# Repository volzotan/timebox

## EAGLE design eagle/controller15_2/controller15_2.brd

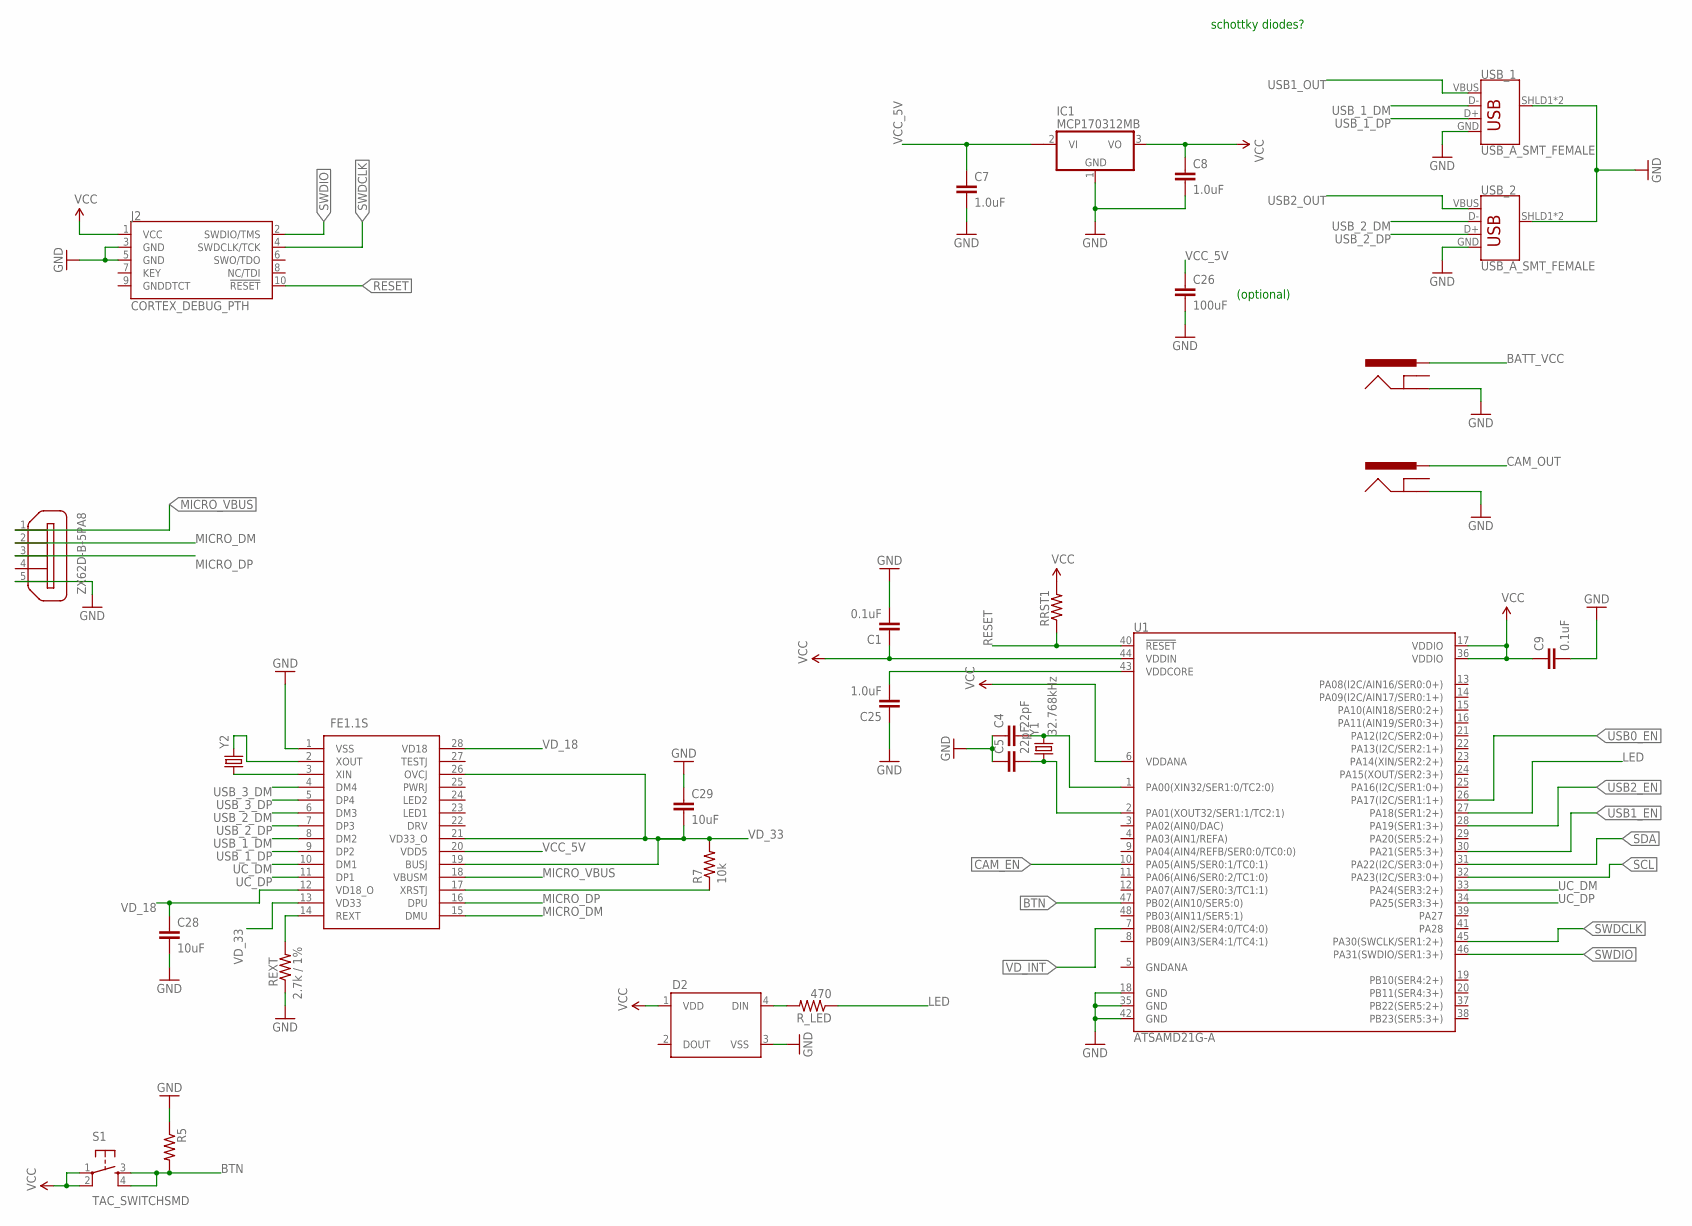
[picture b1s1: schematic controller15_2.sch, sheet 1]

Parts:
C1, C9: 0.1uF; 0805
C4, C5: 22pF; 0805
C7, C8: 1.0uF; 1206
C25: 1.0uF; 0805
C26: 100uF; 1206
C28, C29: 10uF; 0805
D2: WS2812B
IC1: MCP170312MB; SOT89
IC3: FE1.1S; SOP64P600X175-28N
J2: CORTEX_DEBUG_PTH; 2X5-PTH-1.27MM
J3, J4: POWER_JACKPTH_BREAD; POWER_JACK_PTH_BREAD
R5: RESISTOR0805-RES; 0805
R7: 10k; 0805
REXT: 2.7k / 1%; 0805
RRST1: RESISTOR0805-RES; 0805
R_LED: 470; 0805
S1: TAC_SWITCHSMD; TACTILE-SWITCH-SMD
U1: ATSAMD21G-A; TQFP-48
USB_1, USB_2: USB_A_SMT_FEMALE; USB-A-S-SILK-FEMALE
X2: ZX62D-B-5PA8
Y1: 32.768kHz; CRYSTAL-SMD-3.2X1.5MM
Y2: 12MHz; HC49U-V

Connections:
BATT_VCC: J4.PWR; also elsewhere on the board
BTN: R5.2, S1.3, S1.4, U1.47 (PB02(AIN10/SER5:0))
CAM_EN: U1.10 (PA05(AIN5/SER0:1/TC0:1)); also elsewhere on the board
CAM_OUT: J3.PWR; also elsewhere on the board
GND: C1.2, C4.1, C5.1, C7.2, C8.2, C9.2, C25.1, C26.2, C28.2, C29.1, D2.3 (VSS), IC1.1 (GND), IC3.1 (VSS), J2.3 (GND), J2.5 (GND), J3.GND, J4.GND, R5.1, REXT.1, U1.18 (GND), U1.35 (GND), U1.42 (GND), USB_1.GND, USB_1.SHLD1 (SHIELD), USB_1.SHLD2 (SHIELD), USB_2.GND, USB_2.SHLD1 (SHIELD), USB_2.SHLD2 (SHIELD), X2.5; also elsewhere on the board
LED: R_LED.1, U1.27 (PA18(SER1:2+))
MICRO_DM: IC3.15 (DMU), X2.2
MICRO_DP: IC3.16 (DPU), X2.3
MICRO_VBUS: IC3.18 (VBUSM), X2.1; also elsewhere on the board
unnamed: C25.2, U1.43 (VDDCORE)
unnamed: D2.4 (DIN), R_LED.2
unnamed: C4.2, U1.1 (PA00(XIN32/SER1:0/TC2:0)), Y1.P$2 (2)
unnamed: IC3.17 (XRSTJ), R7.1
unnamed: IC3.3 (XIN), Y2.1
unnamed: IC3.2 (XOUT), Y2.2
unnamed: IC3.14 (REXT), REXT.2
unnamed: C5.2, U1.2 (PA01(XOUT32/SER1:1/TC2:1)), Y1.P$1 (1)
RESET: J2.10 (!RESET), RRST1.1, U1.40 (!RESET!)
SCL: U1.32 (PA23(I2C/SER3:0+)); also elsewhere on the board
SDA: U1.31 (PA22(I2C/SER3:0+)); also elsewhere on the board
SWDCLK: J2.4 (SWDCLK/TCK), U1.45 (PA30(SWCLK/SER1:2+))
SWDIO: J2.2 (SWDIO/TMS), U1.46 (PA31(SWDIO/SER1:3+))
UC_DM: IC3.10 (DM1), U1.33 (PA24(SER3:2+))
UC_DP: IC3.11 (DP1), U1.34 (PA25(SER3:3+))
USB0_EN: U1.26 (PA17(I2C/SER1:1+)); also elsewhere on the board
USB1_EN: U1.30 (PA21(SER5:3+)); also elsewhere on the board
USB1_OUT: USB_1.VBUS; also elsewhere on the board
USB2_EN: U1.28 (PA19(SER1:3+)); also elsewhere on the board
USB2_OUT: USB_2.VBUS; also elsewhere on the board
USB_1_DM: IC3.8 (DM2), USB_1.D-
USB_1_DP: IC3.9 (DP2), USB_1.D+
USB_2_DM: IC3.6 (DM3), USB_2.D-
USB_2_DP: IC3.7 (DP3), USB_2.D+
USB_3_DM: IC3.4 (DM4)
USB_3_DP: IC3.5 (DP4)
VCC: C1.1, C8.1, C9.1, D2.1 (VDD), IC1.3 (VO), J2.1 (VCC), RRST1.2, S1.1, S1.2, U1.6 (VDDANA), U1.17 (VDDIO), U1.36 (VDDIO), U1.44 (VDDIN); also elsewhere on the board
VCC_5V: C7.1, C26.1, IC1.2@1 (VI1), IC3.20 (VDD5); also elsewhere on the board
VD_18: C28.1, IC3.12 (VD18_O), IC3.28 (VD18)
VD_33: C29.2, IC3.13 (VD33), IC3.19 (BUSJ), IC3.21 (VD33_O), IC3.26 (OVCJ), R7.2
VD_INT: U1.7 (PB08(AIN2/SER4:0/TC4:0)); also elsewhere on the board

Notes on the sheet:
schottky diodes?
(optional)

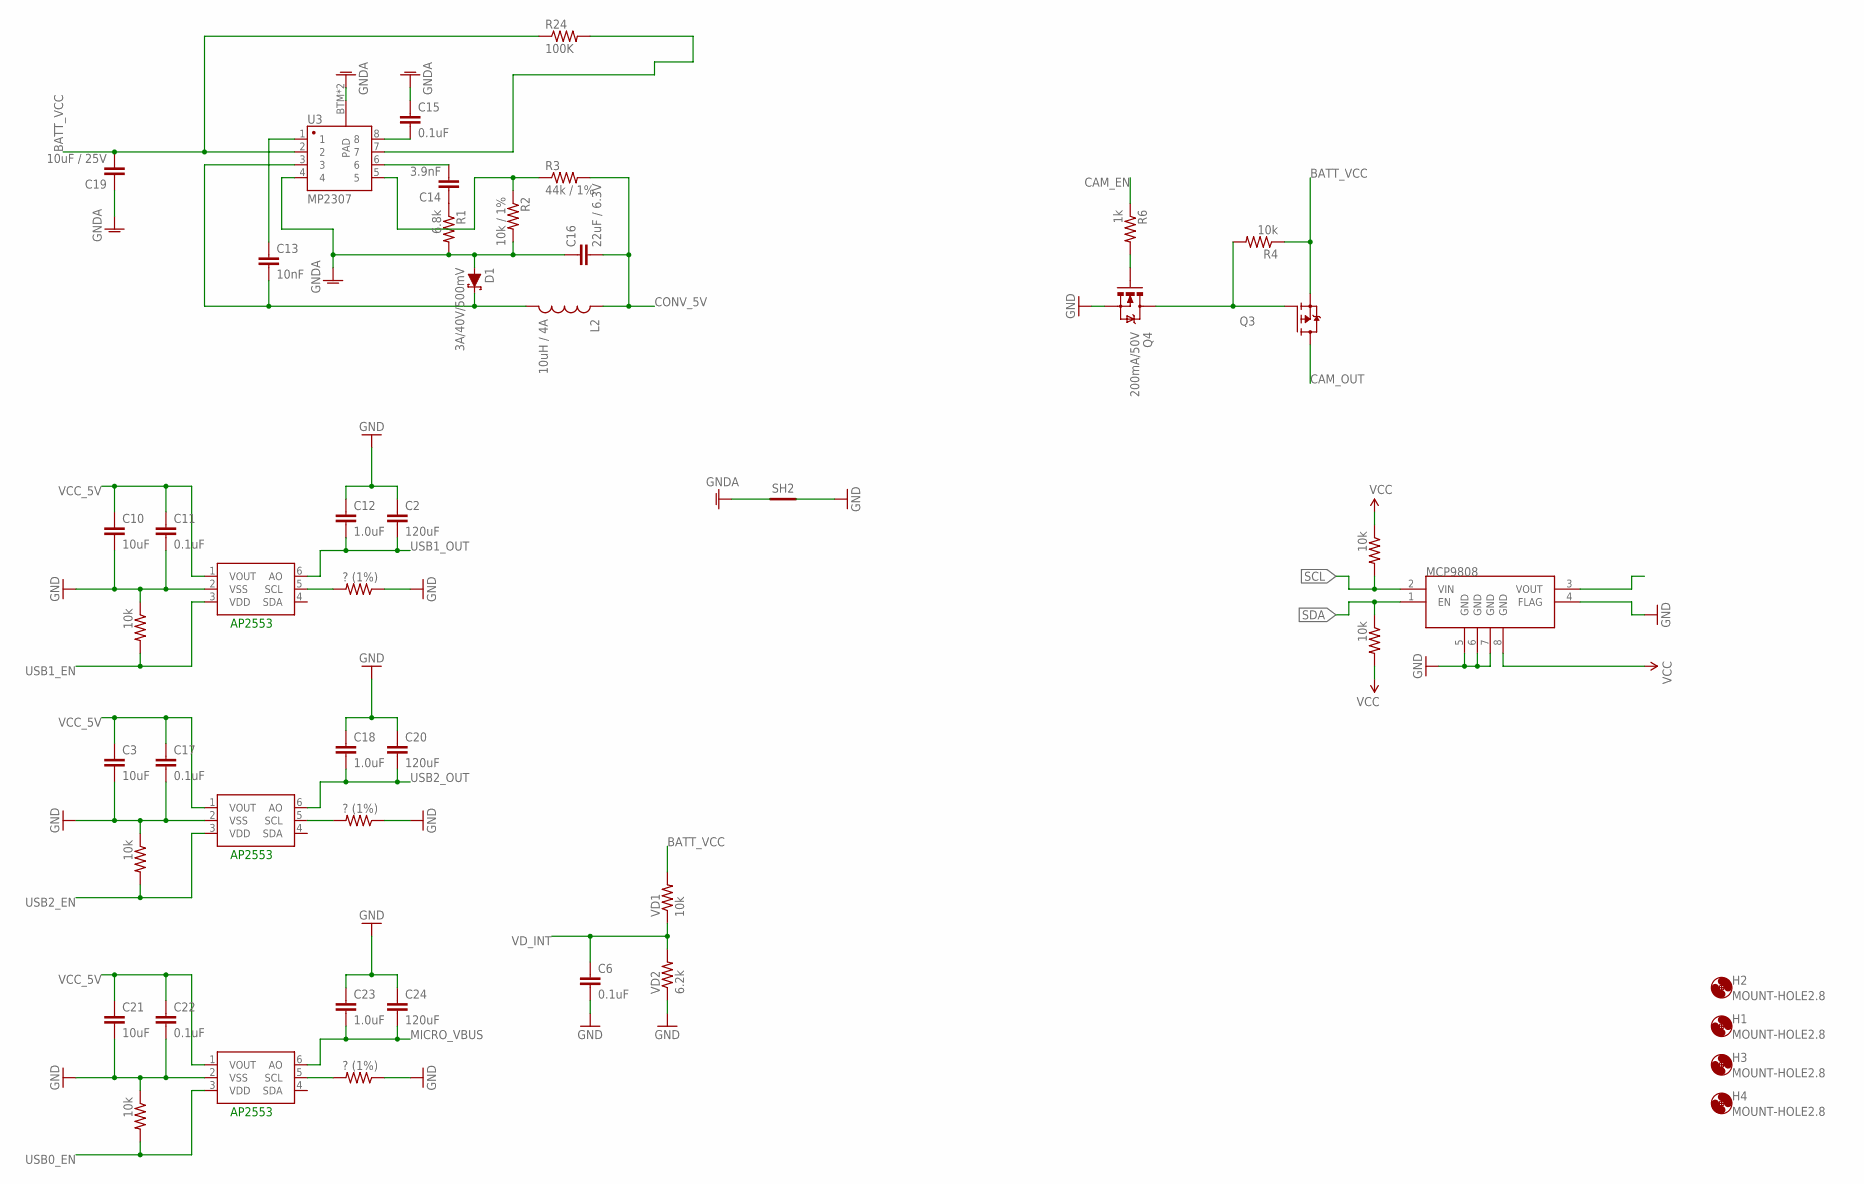
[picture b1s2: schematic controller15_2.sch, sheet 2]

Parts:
AP1, AP2, AP2553: MCP4725; SOT23-6
C2, C20, C24: 120uF; 1206
C3, C10, C21: 10uF; 1206
C6, C15: 0.1uF; 1206
C11, C17, C22: 0.1uF; 0805
C12, C18, C23: 1.0uF; 1206
C13: 10nF; 1206
C14: 3.9nF; 1206
C16: 22uF / 6.3V; 1210
C19: 10uF / 25V; 1210
D1: 3A/40V/500mV; SMA-DIODE
H1, H2, H3, H4: MOUNT-HOLE2.8; 2,8
L2: 10uH / 4A; SRU1038
MCP9808: V_REG_MIC5216; MSOP8
Q3: FDD4141TO252; TO252
Q4: 200mA/50V; SOT23-3
R1: 6.8k; 1206
R2: 10k / 1%; 1206
R3: 44k / 1%; 1206
R4: 10k; 0805
R6: 1k; 0805
R24: 100K; 1206
R_I2C_1, R_I2C_2: 10k; 0805
R_MOSFET_USB1, R_MOSFET_USB2, R_MOSFET_USB5: ? (1%); 0805
R_MOSFET_USB3, R_MOSFET_USB4, R_MOSFET_USB6: 10k; 0805
SH2: SHORT-HT5; SHORT_TOP-50
U3: MP2307; SO08
VD1: 10k; 1206
VD2: 6.2k; 1206

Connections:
BATT_VCC: C19.2, Q3.2 (S), R4.1, R24.1, U3.2, VD1.2; also elsewhere on the board
CAM_EN: R6.1; also elsewhere on the board
CAM_OUT: Q3.3 (D); also elsewhere on the board
CONV_5V: C16.2, L2.1, R3.2
GND: AP1.2 (VSS), AP2.2 (VSS), AP2553.2 (VSS), C2.1, C3.2, C6.2, C10.2, C11.2, C12.1, C17.2, C18.1, C20.1, C21.2, C22.2, C23.1, C24.1, MCP9808.4 (FLAG), MCP9808.5 (GND), MCP9808.6 (GND), MCP9808.7 (GND), Q4.2 (S), R_MOSFET_USB1.1, R_MOSFET_USB2.1, R_MOSFET_USB3.1, R_MOSFET_USB4.1, R_MOSFET_USB5.1, R_MOSFET_USB6.1, SH2.2, VD2.1; also elsewhere on the board
GNDA: C15.1, C16.1, C19.1, D1.A, R1.2, R2.2, SH2.1, U3.4, U3.BTM (PAD), U3.P$1 (PAD)
MICRO_VBUS: AP2.6 (AO), C23.2, C24.2; also elsewhere on the board
unnamed: Q4.1 (G), R6.2
unnamed: Q3.1 (G), Q4.3 (D), R4.2
unnamed: AP2553.5 (SCL), R_MOSFET_USB1.2
unnamed: AP1.5 (SCL), R_MOSFET_USB2.2
unnamed: AP2.5 (SCL), R_MOSFET_USB5.2
unnamed: C15.2, U3.8
unnamed: C13.2, D1.C, L2.2, U3.3
unnamed: C13.1, U3.1
unnamed: C14.1, R1.1
unnamed: C14.2, U3.6
unnamed: R2.1, R3.1, U3.5
PB_BUCK_EN: R24.2, U3.7
SCL: MCP9808.2 (VIN), R_I2C_1.2; also elsewhere on the board
SDA: MCP9808.1 (EN), R_I2C_2.1; also elsewhere on the board
USB0_EN: AP2.3 (VDD), R_MOSFET_USB6.2; also elsewhere on the board
USB1_EN: AP2553.3 (VDD), R_MOSFET_USB3.2; also elsewhere on the board
USB1_OUT: AP2553.6 (AO), C2.2, C12.2; also elsewhere on the board
USB2_EN: AP1.3 (VDD), R_MOSFET_USB4.2; also elsewhere on the board
USB2_OUT: AP1.6 (AO), C18.2, C20.2; also elsewhere on the board
VCC: MCP9808.8 (GND), R_I2C_1.1, R_I2C_2.2; also elsewhere on the board
VCC_5V: AP1.1 (VOUT), AP2.1 (VOUT), AP2553.1 (VOUT), C3.1, C10.1, C11.1, C17.1, C21.1, C22.1; also elsewhere on the board
VD_INT: C6.1, VD1.1, VD2.2; also elsewhere on the board

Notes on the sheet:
AP2553

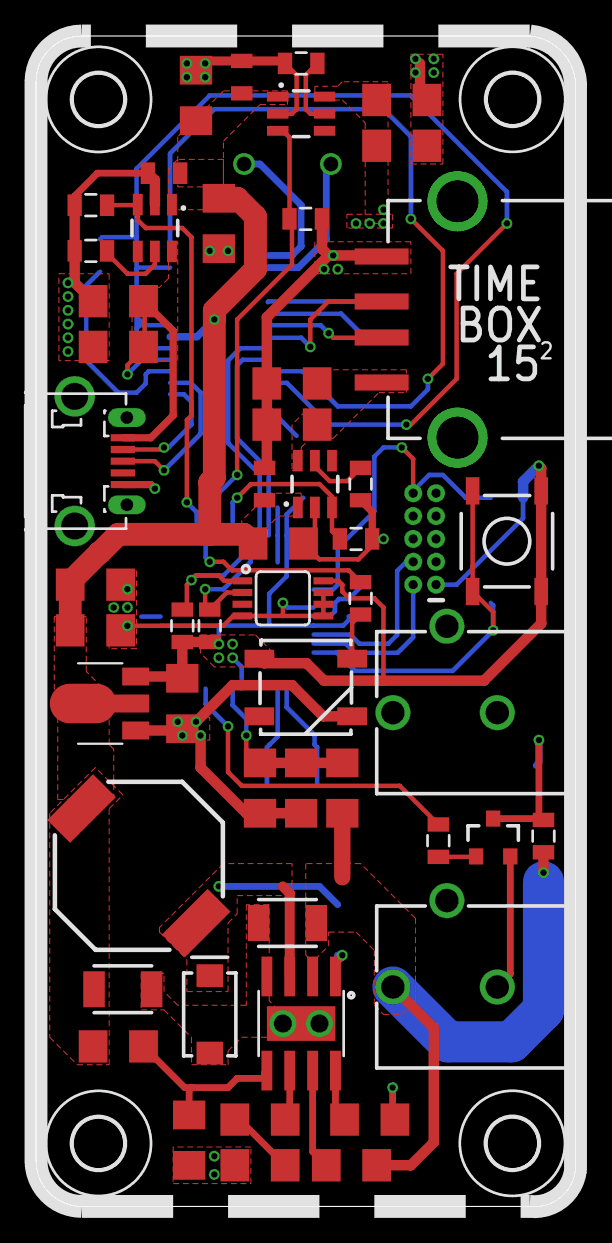
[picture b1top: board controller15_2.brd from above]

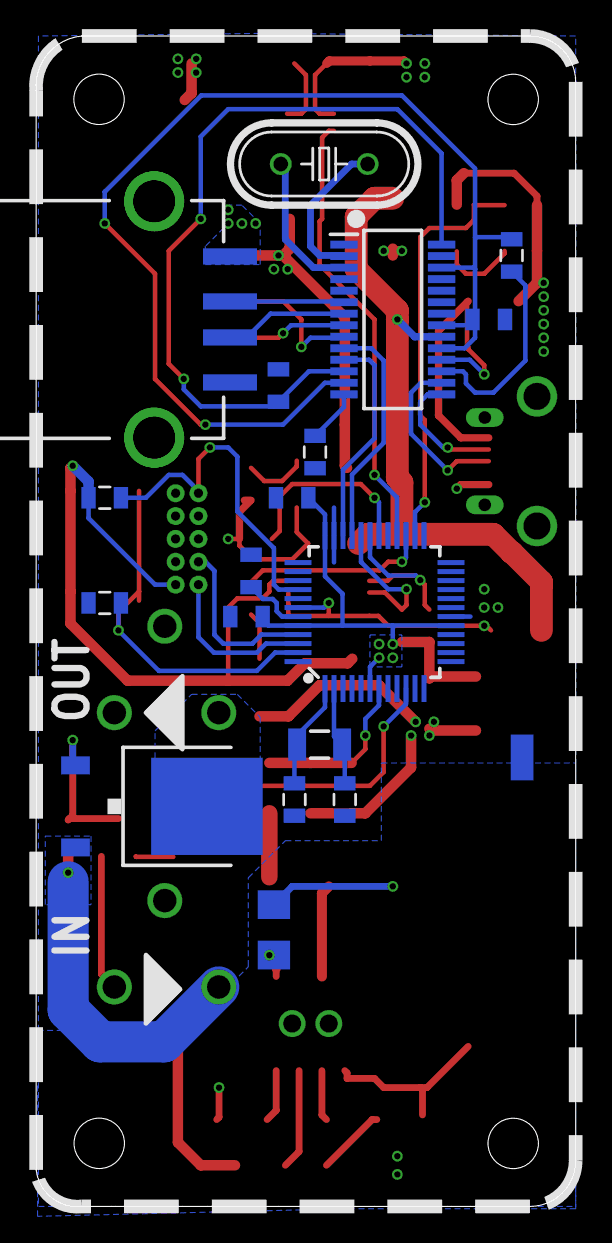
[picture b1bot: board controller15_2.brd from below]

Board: 2 copper layers, 30.0 x 65.0 mm, 76 parts (19 on the bottom side), 52 nets.

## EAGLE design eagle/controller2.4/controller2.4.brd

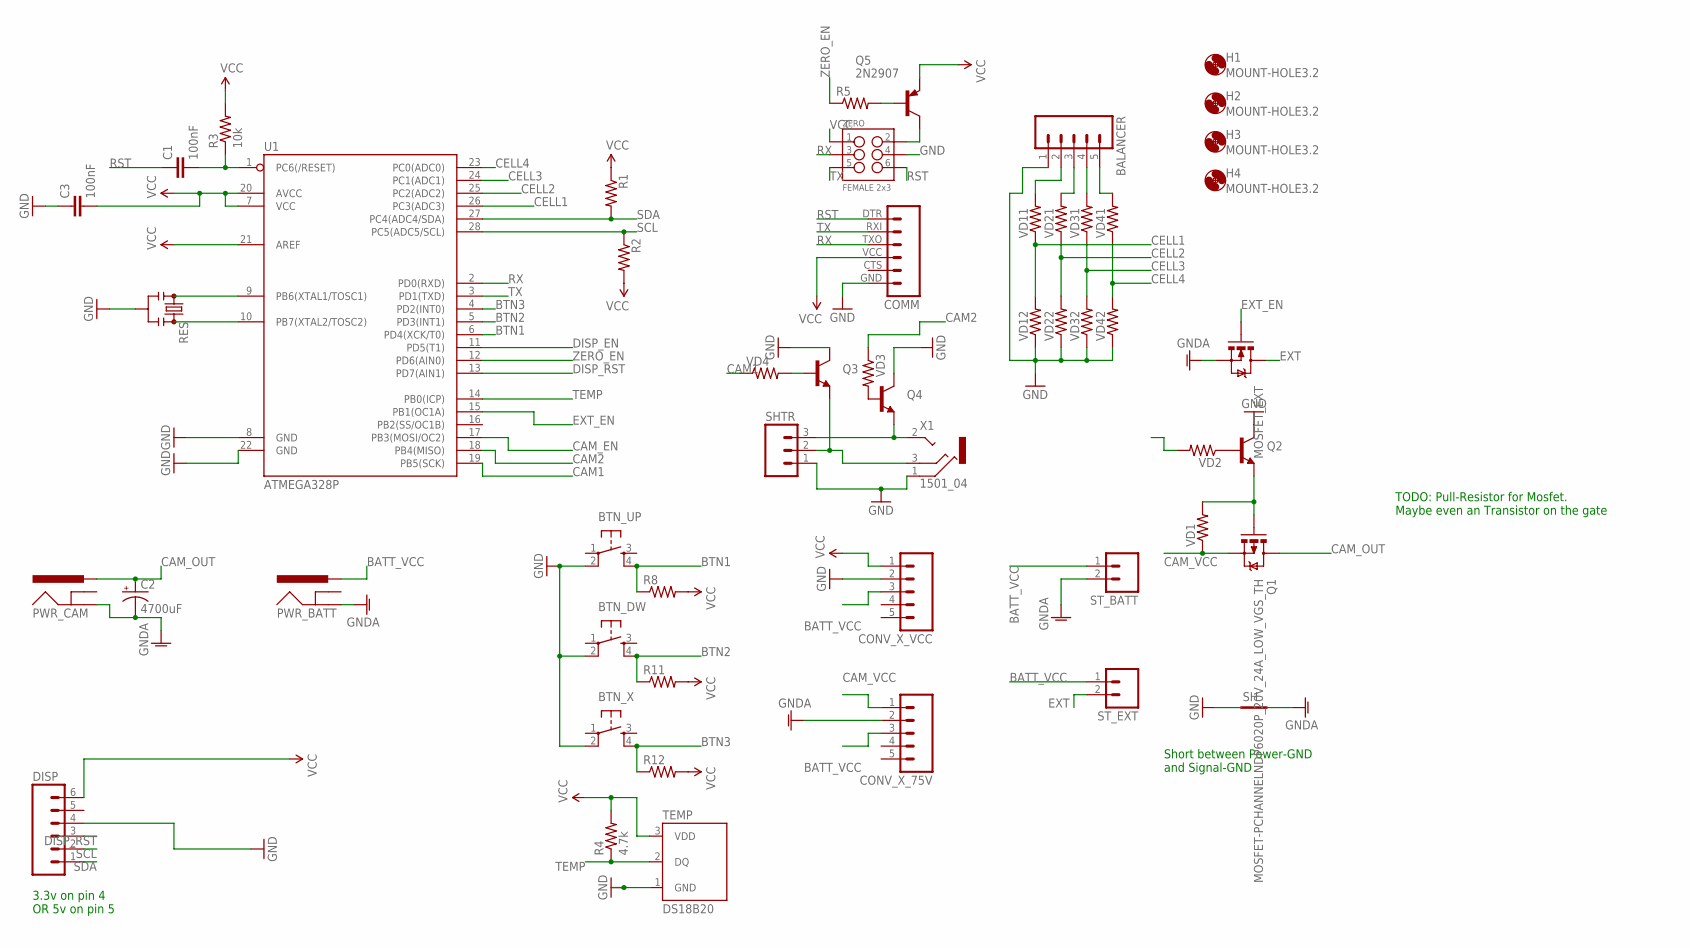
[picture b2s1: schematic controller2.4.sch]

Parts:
BALANCER: M05LOCK; 1X05_LOCK
BTN_DW: TAC_SWITCHPTH; TACTILE-PTH
BTN_UP: TAC_SWITCHPTH; TACTILE-PTH
BTN_X: TAC_SWITCHPTH; TACTILE-PTH
C1, C3: 100nF; CAP-PTH-SMALL
C2: 4700uF; CPOL-RADIAL-1000UF-63V
COMM: FTDI_BASICPTH; FTDI_BASIC
CONV_X_75V: M05LOCK; 1X05_LOCK
CONV_X_VCC: M05LOCK; 1X05_LOCK
DISP: M06FEMALE_LOCK; 1X06_FEMALE_LOCK.010
H1, H2, H3, H4: MOUNT-HOLE3.2; 3,2
MOSFET_EXT: MOSFET-NCHANNELFQP30N06L; TO220V
PWR_BATT: POWER_JACKPTH_BREAD; POWER_JACK_PTH_BREAD
PWR_CAM: POWER_JACKPTH_BREAD; POWER_JACK_PTH_BREAD
Q1: MOSFET-PCHANNELNDP6020P_20V_24A_LOW_VGS_TH; TO220V
Q2, Q3, Q4: TRANSISTOR_NPN2N3904; TO-92
Q5: 2N2907; TO92-EBC-OVAL
R1, R2, R5, R8, R11, R12: RESISTORAXIAL-0.3; AXIAL-0.3
R3: 10k; AXIAL-0.3
R4: 4.7k; AXIAL-0.3
RES: RESONATORPTH; RESONATOR-PTH
SH: SHORT-HT5; SHORT_TOP-50
SHTR: M03LOCK; 1X03_LOCK
ST_BATT: M025MM; SCREWTERMINAL-5MM-2
ST_EXT: M025MM; SCREWTERMINAL-5MM-2
TEMP: DS18B20; TO-92-AMMO
U1: ATMEGA328P; DIL28-3
VD1, VD2, VD3, VD4, VD11, VD12, VD21, VD22, VD31, VD32, VD41, VD42: RESISTORAXIAL-0.3; AXIAL-0.3
X1: 1501_04; 1501_05
ZERO: FEMALE 2x3; 2X3

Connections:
BATT_VCC: CONV_X_75V.3, CONV_X_VCC.3, PWR_BATT.PWR, ST_BATT.1, ST_EXT.1
BTN1: BTN_UP.4, R8.P$1 (1), U1.6 (PD4(XCK/T0))
BTN2: BTN_DW.4, R11.P$1 (1), U1.5 (PD3(INT1))
BTN3: BTN_X.4, R12.P$1 (1), U1.4 (PD2(INT0))
CAM1: U1.19 (PB5(SCK)), VD4.P$1 (1)
CAM2: U1.18 (PB4(MISO)), VD3.P$1 (1)
CAM_EN: U1.17 (PB3(MOSI/OC2)), VD2.P$2 (2)
CAM_OUT: C2.1 (+), PWR_CAM.PWR, Q1.2 (D)
CAM_VCC: CONV_X_75V.1, Q1.3 (S), VD1.P$1 (1)
CELL1: U1.26 (PC3(ADC3)), VD11.P$1 (1), VD12.P$2 (2)
CELL2: U1.25 (PC2(ADC2)), VD21.P$1 (1), VD22.P$2 (2)
CELL3: U1.24 (PC1(ADC1)), VD31.P$1 (1), VD32.P$2 (2)
CELL4: U1.23 (PC0(ADC0)), VD41.P$1 (1), VD42.P$2 (2)
DISP_EN: U1.11 (PD5(T1))
DISP_RST: DISP.3, U1.13 (PD7(AIN1))
EXT: MOSFET_EXT.2 (D), ST_EXT.2
EXT_EN: MOSFET_EXT.1 (G), U1.15 (PB1(OC1A))
GND: BALANCER.1, BTN_DW.2, BTN_UP.2, BTN_X.2, C3.1, COMM.GND (6), CONV_X_VCC.2, DISP.4, Q2.3 (C), Q3.3 (C), Q4.3 (C), RES.2, SH.1, SHTR.1, TEMP.1 (GND), U1.8 (GND), U1.22 (GND), VD12.P$1 (1), VD22.P$1 (1), VD32.P$1 (1), VD42.P$1 (1), X1.1, ZERO.4
GNDA: C2.2 (-), CONV_X_75V.2, MOSFET_EXT.3 (S), PWR_BATT.GND, PWR_CAM.GND, SH.2, ST_BATT.2
unnamed: C1.2, R3.P$1 (1), U1.1 (PC6(/RESET))
unnamed: Q1.1 (G), Q2.1 (E), VD1.P$2 (2)
unnamed: Q3.1 (E), SHTR.2, X1.3
unnamed: BALANCER.2, VD11.P$2 (2)
unnamed: BALANCER.3, VD21.P$2 (2)
unnamed: Q4.1 (E), SHTR.3, X1.2
unnamed: Q2.2 (B), VD2.P$1 (1)
unnamed: RES.3, U1.10 (PB7(XTAL2/TOSC2))
unnamed: RES.1, U1.9 (PB6(XTAL1/TOSC1))
unnamed: BALANCER.4, VD31.P$2 (2)
unnamed: BALANCER.5, VD41.P$2 (2)
unnamed: Q5.C, ZERO.2
unnamed: Q3.2 (B), VD4.P$2 (2)
unnamed: Q4.2 (B), VD3.P$2 (2)
unnamed: Q5.B, R5.P$2 (2)
RST: C1.1, COMM.DTR (1), ZERO.6
RX: COMM.TXO (3), U1.2 (PD0(RXD)), ZERO.3
SCL: DISP.2, R2.P$1 (1), U1.28 (PC5(ADC5/SCL))
SDA: DISP.1, R1.P$2 (2), U1.27 (PC4(ADC4/SDA))
TEMP: R4.P$1 (1), TEMP.2 (DQ), U1.14 (PB0(ICP))
TX: COMM.RXI (2), U1.3 (PD1(TXD)), ZERO.5
VCC: C3.2, COMM.VCC (4), CONV_X_VCC.1, DISP.6, Q5.E, R1.P$1 (1), R2.P$2 (2), R3.P$2 (2), R4.P$2 (2), R8.P$2 (2), R11.P$2 (2), R12.P$2 (2), TEMP.3 (VDD), U1.7 (VCC), U1.20 (AVCC), U1.21 (AREF), ZERO.1
ZERO_EN: R5.P$1 (1), U1.12 (PD6(AIN0))

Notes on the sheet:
3.3v on pin 4 OR 5v on pin 5
Short between Power-GND and Signal-GND
TODO: Pull-Resistor for Mosfet. Maybe even an Transistor on the gate

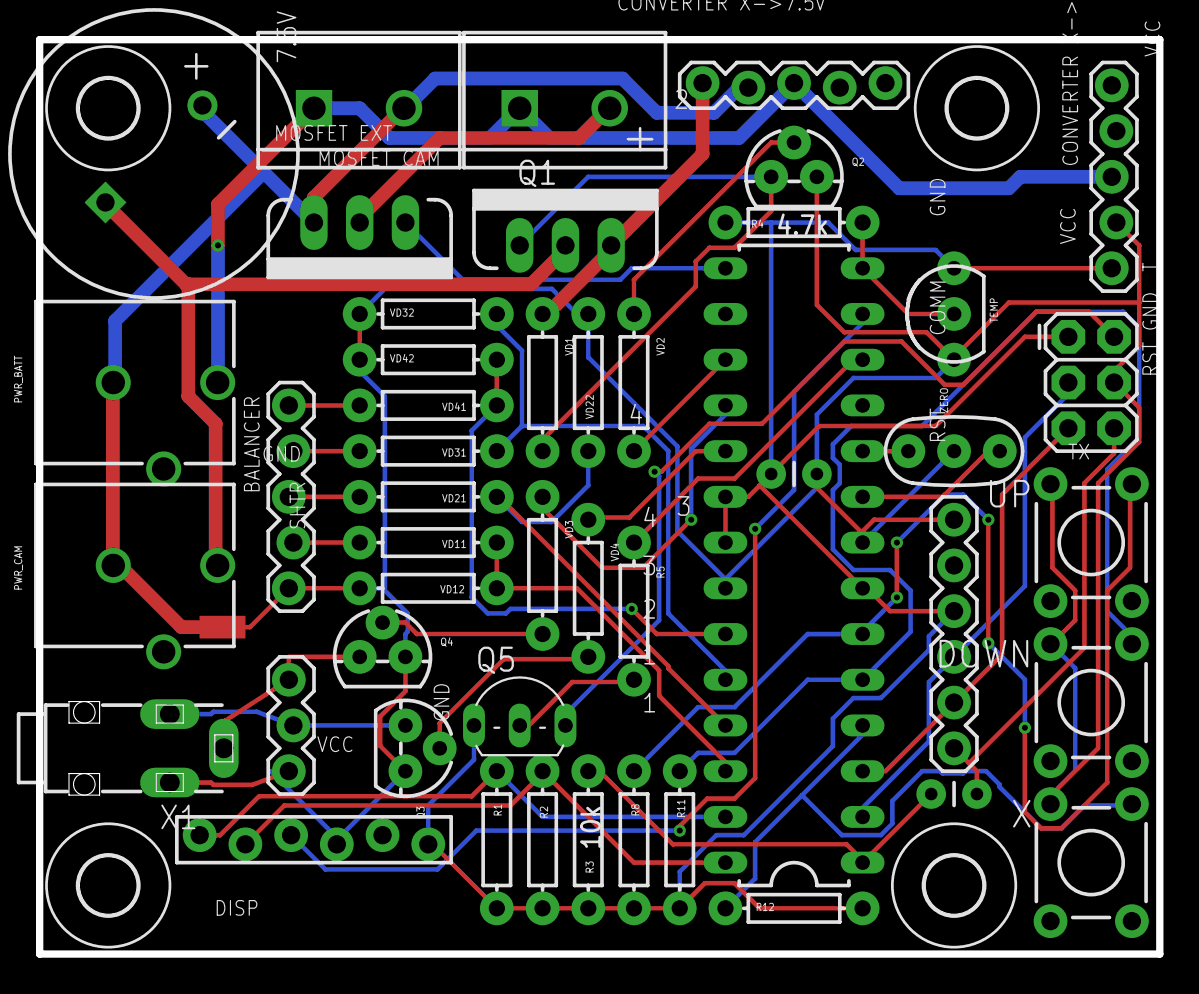
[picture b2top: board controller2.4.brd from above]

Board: 2 copper layers, 62.2 x 50.8 mm, 52 parts (0 on the bottom side), 41 nets.

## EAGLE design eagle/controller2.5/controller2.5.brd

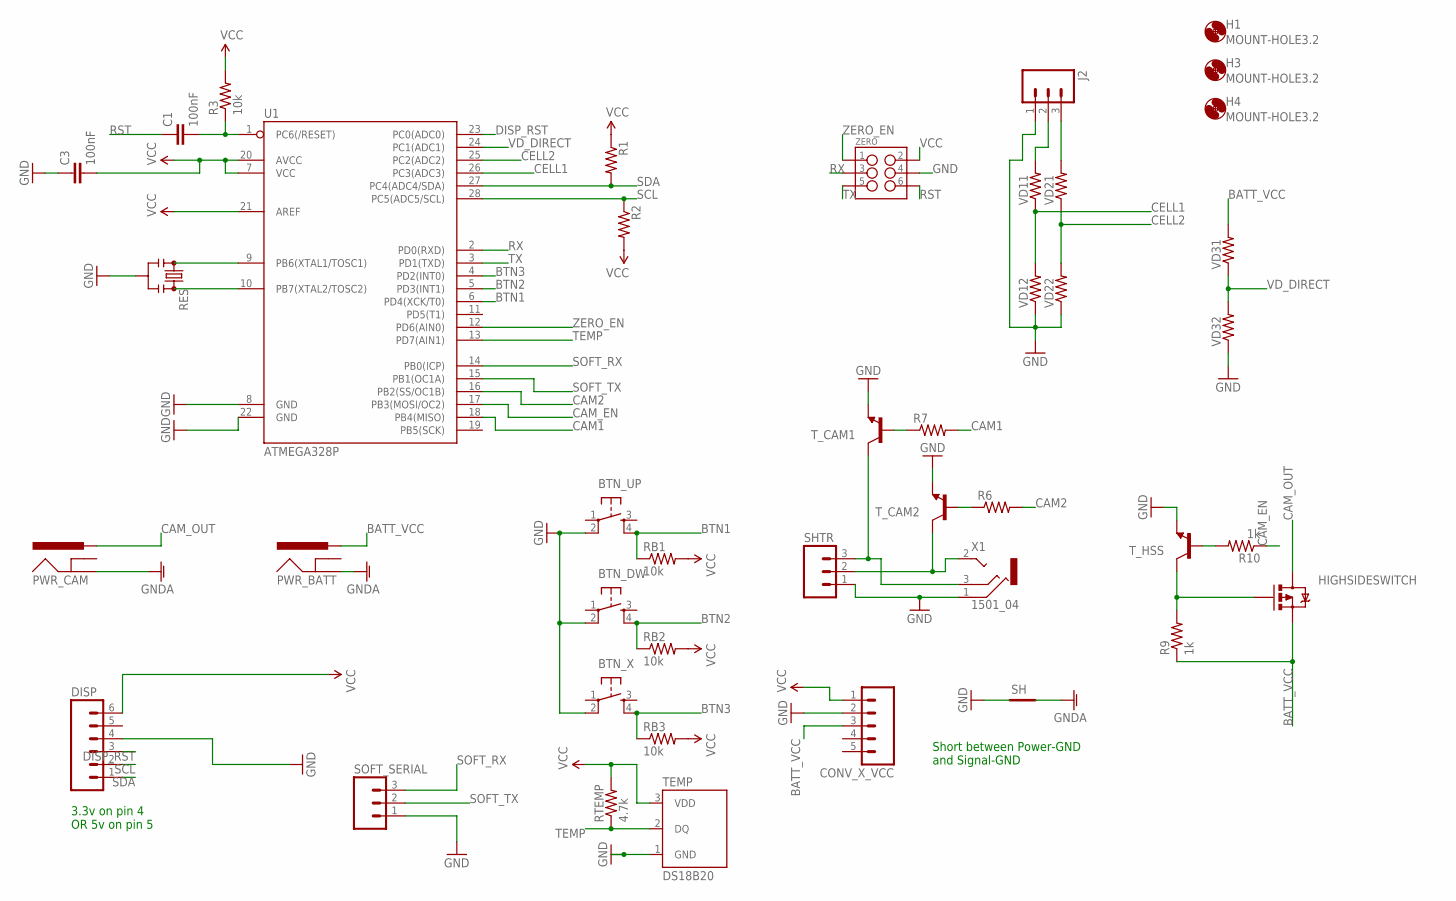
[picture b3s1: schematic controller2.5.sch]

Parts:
BTN_DW: TAC_SWITCHPTH; TACTILE-PTH
BTN_UP: TAC_SWITCHPTH; TACTILE-PTH
BTN_X: TAC_SWITCHPTH; TACTILE-PTH
C1, C3: 100nF; CAP-PTH-SMALL
CONV_X_VCC: M05LOCK; 1X05_LOCK
DISP: M06FEMALE_LOCK; 1X06_FEMALE_LOCK.010
H1, H3, H4: MOUNT-HOLE3.2; 3,2
HIGHSIDESWITCH: MOSFET-PCHANNELNDP6020P_20V_24A_LOW_VGS_TH; TO220V
J2: M03LOCK; 1X03_LOCK
PWR_BATT: POWER_JACKPTH_BREAD; POWER_JACK_PTH_BREAD
PWR_CAM: POWER_JACKPTH_BREAD; POWER_JACK_PTH_BREAD
R1, R2, R6, R7: RESISTORAXIAL-0.3; AXIAL-0.3
R3: 10k; AXIAL-0.3
R9, R10: 1k; AXIAL-0.3
RB1, RB2, RB3: 10k; AXIAL-0.3
RES: RESONATORPTH; RESONATOR-PTH
RTEMP: 4.7k; AXIAL-0.3
SH: SHORT-HT5; SHORT_TOP-50
SHTR: M03LOCK; 1X03_LOCK
SOFT_SERIAL: M03LOCK; 1X03_LOCK
TEMP: DS18B20; TO-92-AMMO
T_CAM1, T_CAM2: TRANSISTOR_NPN2N3904; TO-92
T_HSS: TRANSISTOR_NPN2N3904; TO-92
U1: ATMEGA328P; DIL28-3
VD11, VD12, VD21, VD22, VD31, VD32: RESISTORAXIAL-0.3; AXIAL-0.3
X1: 1501_04; 1501_05
ZERO: M03X2FEMALE; 2X3

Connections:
BATT_VCC: CONV_X_VCC.3, HIGHSIDESWITCH.3 (S), PWR_BATT.PWR, R9.P$1 (1), VD31.P$2 (2)
BTN1: BTN_UP.4, RB1.P$1 (1), U1.6 (PD4(XCK/T0))
BTN2: BTN_DW.4, RB2.P$1 (1), U1.5 (PD3(INT1))
BTN3: BTN_X.4, RB3.P$1 (1), U1.4 (PD2(INT0))
CAM1: R7.P$2 (2), U1.18 (PB4(MISO))
CAM2: R6.P$2 (2), U1.16 (PB2(SS/OC1B))
CAM_EN: R10.P$1 (1), U1.17 (PB3(MOSI/OC2))
CAM_OUT: HIGHSIDESWITCH.2 (D), PWR_CAM.PWR
CELL1: U1.26 (PC3(ADC3)), VD11.P$1 (1), VD12.P$2 (2)
CELL2: U1.25 (PC2(ADC2)), VD21.P$1 (1), VD22.P$2 (2)
DISP_RST: DISP.3, U1.23 (PC0(ADC0))
GND: BTN_DW.2, BTN_UP.2, BTN_X.2, C3.1, CONV_X_VCC.2, DISP.4, J2.1, RES.2, SH.1, SHTR.1, SOFT_SERIAL.1, TEMP.1 (GND), T_CAM1.1 (E), T_CAM2.1 (E), T_HSS.1 (E), U1.8 (GND), U1.22 (GND), VD12.P$1 (1), VD22.P$1 (1), VD32.P$1 (1), X1.1, ZERO.4
GNDA: PWR_BATT.GND, PWR_CAM.GND, SH.2
unnamed: C1.2, R3.P$1 (1), U1.1 (PC6(/RESET))
unnamed: J2.2, VD11.P$2 (2)
unnamed: R7.P$1 (1), T_CAM1.2 (B)
unnamed: J2.3, VD21.P$2 (2)
unnamed: SHTR.2, T_CAM2.3 (C), X1.2
unnamed: RES.3, U1.10 (PB7(XTAL2/TOSC2))
unnamed: RES.1, U1.9 (PB6(XTAL1/TOSC1))
unnamed: SHTR.3, T_CAM1.3 (C), X1.3
unnamed: R6.P$1 (1), T_CAM2.2 (B)
unnamed: R10.P$2 (2), T_HSS.2 (B)
unnamed: HIGHSIDESWITCH.1 (G), R9.P$2 (2), T_HSS.3 (C)
RST: C1.1, ZERO.6
RX: U1.2 (PD0(RXD)), ZERO.3
SCL: DISP.2, R2.P$1 (1), U1.28 (PC5(ADC5/SCL))
SDA: DISP.1, R1.P$2 (2), U1.27 (PC4(ADC4/SDA))
SOFT_RX: SOFT_SERIAL.3, U1.14 (PB0(ICP))
SOFT_TX: SOFT_SERIAL.2, U1.15 (PB1(OC1A))
TEMP: RTEMP.P$1 (1), TEMP.2 (DQ), U1.13 (PD7(AIN1))
TX: U1.3 (PD1(TXD)), ZERO.5
VCC: C3.2, CONV_X_VCC.1, DISP.6, R1.P$1 (1), R2.P$2 (2), R3.P$2 (2), RB1.P$2 (2), RB2.P$2 (2), RB3.P$2 (2), RTEMP.P$2 (2), TEMP.3 (VDD), U1.7 (VCC), U1.20 (AVCC), U1.21 (AREF), ZERO.2
VD_DIRECT: U1.24 (PC1(ADC1)), VD31.P$1 (1), VD32.P$2 (2)
ZERO_EN: U1.12 (PD6(AIN0)), ZERO.1

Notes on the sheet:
3.3v on pin 4 OR 5v on pin 5
Short between Power-GND and Signal-GND

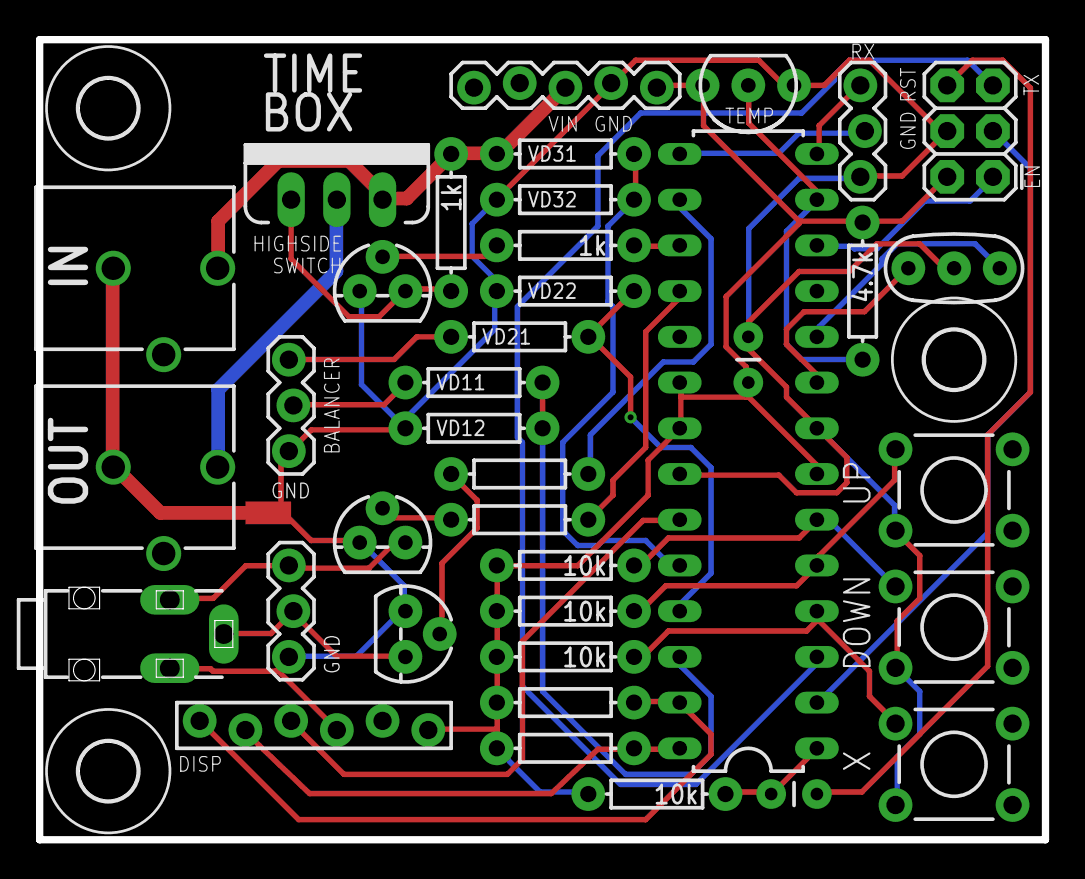
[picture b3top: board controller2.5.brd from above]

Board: 2 copper layers, 55.9 x 44.5 mm, 42 parts (0 on the bottom side), 35 nets.

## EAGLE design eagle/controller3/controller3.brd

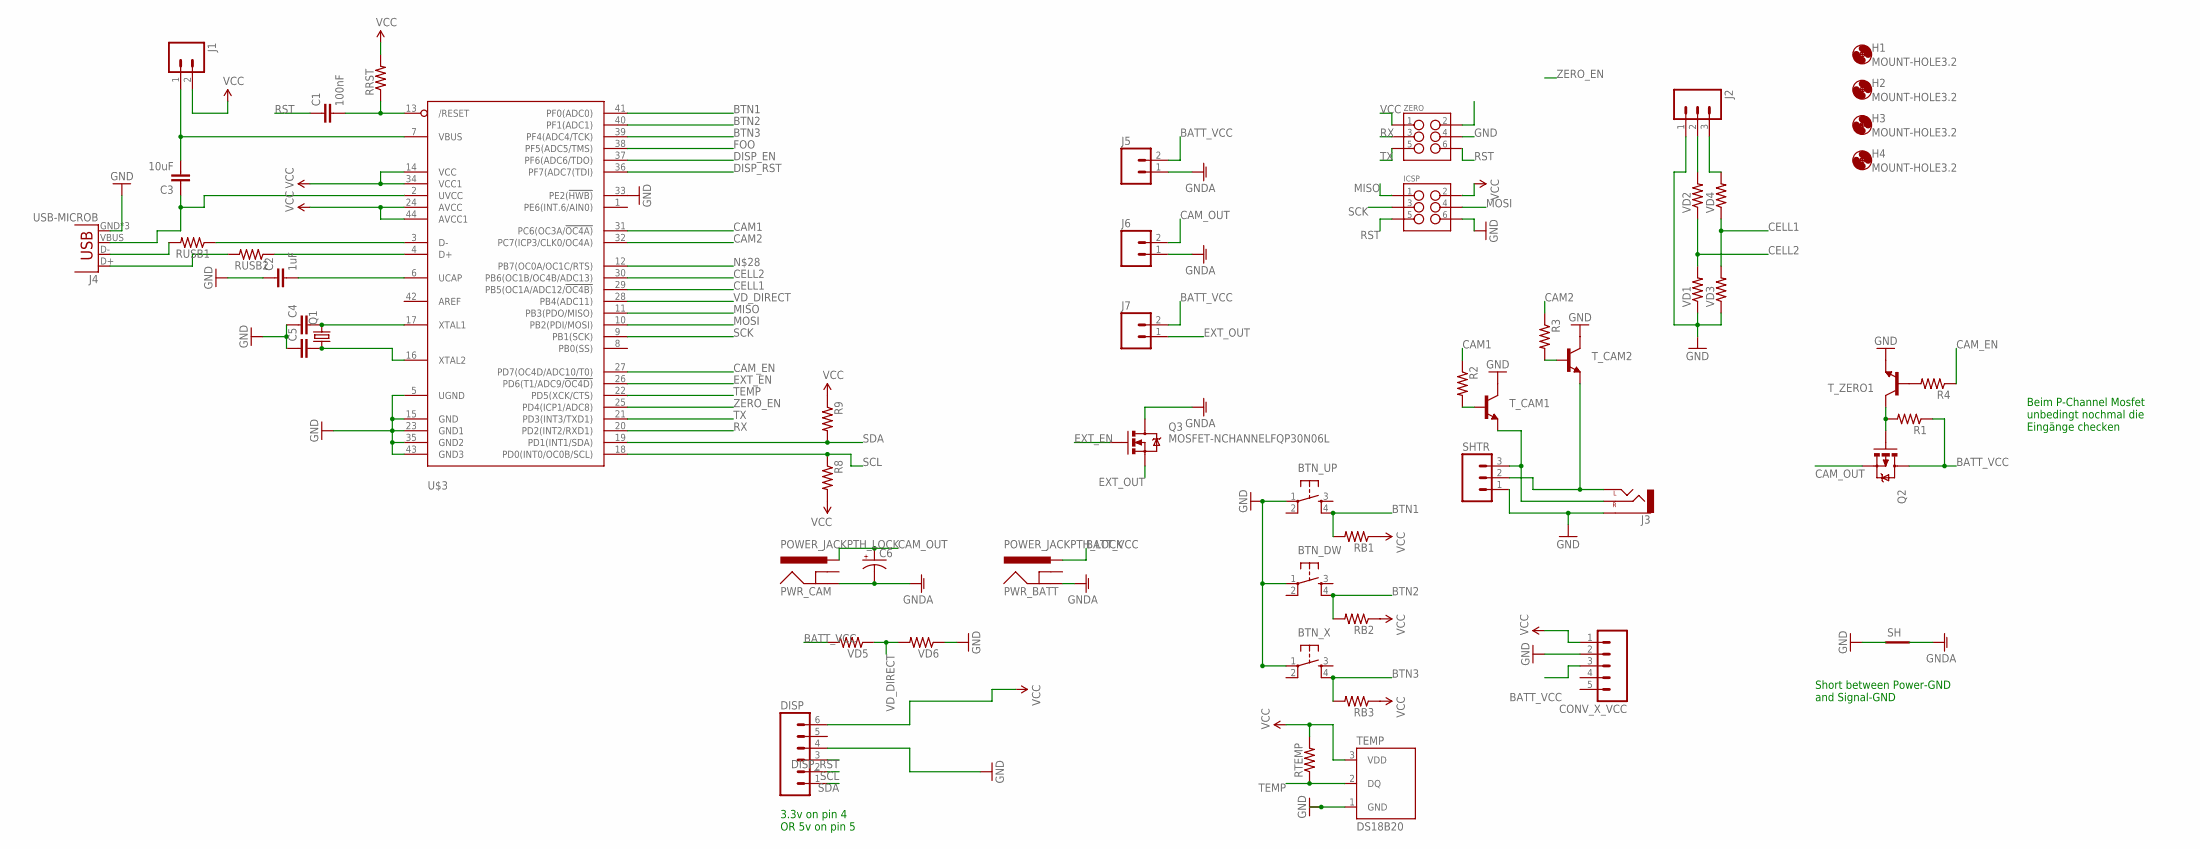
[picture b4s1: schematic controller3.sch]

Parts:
BTN_DW: TAC_SWITCHPTH; TACTILE-PTH
BTN_UP: TAC_SWITCHPTH; TACTILE-PTH
BTN_X: TAC_SWITCHPTH; TACTILE-PTH
C1: 100nF; 1206
C2: 1uF; 1206
C3: 10uF; 1206
C4, C5: CAP1206; 1206
C6: CAP_POLPTH3; CPOL-RADIAL-1000UF-63V
CONV_X_VCC: M05LOCK; 1X05_LOCK
DISP: M06FEMALE_LOCK; 1X06_FEMALE_LOCK.010
H1, H2, H3, H4: MOUNT-HOLE3.2; 3,2
ICSP: M03X2FEMALE; 2X3
J1: M02LOCK; 1X02_LOCK
J2: M03LOCK; 1X03_LOCK
J3: AUDIO-JACK2.5MM; STEREOJACK2.5MM_STEREOJACK2.5MM
J4: USB-MICROB
J5, J6, J7: M025MM; SCREWTERMINAL-5MM-2
PWR_BATT: POWER_JACKPTH_LOCK; POWER_JACK_PTH_LOCK
PWR_CAM: POWER_JACKPTH_LOCK; POWER_JACK_PTH_LOCK
Q1: CRYSTALHC49S; HC49/S
Q2: MOSFET-PCHANNELFQP27P06; TO220V
Q3: MOSFET-NCHANNELFQP30N06L; TO220V
R1, R2, R3, R4, R8, R9: RESISTOR1206; 1206
RB1, RB2, RB3: RESISTOR1206; 1206
RRST: RESISTOR1206; 1206
RTEMP: RESISTOR1206; 1206
RUSB1, RUSB2: RESISTOR1206; 1206
SH: SHORT-HT5; SHORT_TOP-50
SHTR: M03LOCK; 1X03_LOCK
TEMP: DS18B20; TO-92-AMMO
T_CAM1, T_CAM2: TRANSISTOR_NPN2N3904; TO-92
T_ZERO1: TRANSISTOR_NPN2N3904; TO-92
U$3: ATMEGA32U4-AU; TQFP44
VD1, VD2, VD3, VD4, VD5, VD6: RESISTOR1206; 1206
ZERO: M03X2FEMALE; 2X3

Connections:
BATT_VCC: CONV_X_VCC.3, J5.2, J7.2, PWR_BATT.PWR, Q2.2 (D), R1.1, VD5.2
BTN1: BTN_UP.4, RB1.2, U$3.41 (PF0(ADC0))
BTN2: BTN_DW.4, RB2.2, U$3.40 (PF1(ADC1))
BTN3: BTN_X.4, RB3.2, U$3.39 (PF4(ADC4/TCK))
CAM1: R2.1, U$3.31 (PC6(OC3A/!OC4A))
CAM2: R3.1, U$3.32 (PC7(ICP3/CLK0/OC4A))
CAM_EN: R4.1, U$3.27 (PD7(OC4D/ADC10/T0))
CAM_OUT: C6.1 (+), J6.2, PWR_CAM.PWR, Q2.3 (S)
CELL1: U$3.29 (PB5(OC1A/ADC12/!OC4B)), VD3.2, VD4.1
CELL2: U$3.30 (PB6(OC1B/OC4B/ADC13)), VD1.2, VD2.1
DISP_EN: U$3.37 (PF6(ADC6/TDO))
DISP_RST: DISP.3, U$3.36 (PF7(ADC7(TDI))
EXT_EN: Q3.1 (G), U$3.26 (PD6(T1/ADC9/!OC4D))
EXT_OUT: J7.1, Q3.3 (S)
FOO: U$3.38 (PF5(ADC5/TMS))
GND: BTN_DW.1, BTN_UP.1, BTN_X.1, C2.1, C4.1, C5.1, CONV_X_VCC.2, DISP.4, ICSP.6, J2.1, J3.SHIELD (SLEEVE), J4.GND, J4.MT1 (GND), J4.MT2 (GND), SH.1, SHTR.1, TEMP.1 (GND), T_CAM1.3 (C), T_CAM2.3 (C), T_ZERO1.1 (E), U$3.5 (UGND), U$3.15 (GND), U$3.23 (GND1), U$3.33 (PE2(!HWB)), U$3.35 (GND2), U$3.43 (GND3), VD1.1, VD3.1, VD6.1, ZERO.4
GNDA: C6.2 (-), J5.1, J6.1, PWR_BATT.GND, PWR_CAM.GND, Q3.2 (D), SH.2
MISO: ICSP.1, U$3.11 (PB3(PDO/MISO))
MOSI: ICSP.4, U$3.10 (PB2(PDI/MOSI))
unnamed: C1.2, RRST.1, U$3.13 (/RESET)
unnamed: J2.3, VD4.2
unnamed: J2.2, VD2.2
unnamed: RUSB1.1, U$3.3 (D-)
unnamed: RUSB2.1, U$3.4 (D+)
unnamed: C3.1, J4.VBUS, U$3.2 (UVCC)
unnamed: R4.2, T_ZERO1.2 (B)
unnamed: C4.2, Q1.2, U$3.17 (XTAL1)
unnamed: C5.2, Q1.1, U$3.16 (XTAL2)
unnamed: C3.2, J1.1, U$3.7 (VBUS)
unnamed: J4.D-, RUSB1.2
unnamed: J4.D+, RUSB2.2
unnamed: J3.RING (RIGHT), SHTR.3, T_CAM1.1 (E)
unnamed: J3.TIP (LEFT), SHTR.2, T_CAM2.1 (E)
unnamed: R2.2, T_CAM1.2 (B)
unnamed: R3.2, T_CAM2.2 (B)
unnamed: C2.2, U$3.6 (UCAP)
unnamed: Q2.1 (G), R1.2, T_ZERO1.3 (C)
RST: C1.1, ICSP.5, ZERO.6
RX: U$3.20 (PD2(INT2/RXD1)), ZERO.3
SCK: ICSP.3, U$3.9 (PB1(SCK))
SCL: DISP.2, R8.1, U$3.18 (PD0(INT0/OC0B/SCL))
SDA: DISP.1, R9.2, U$3.19 (PD1(INT1/SDA))
TEMP: RTEMP.1, TEMP.2 (DQ), U$3.22 (PD5(XCK/CTS))
TX: U$3.21 (PD3(INT3/TXD1)), ZERO.5
VCC: CONV_X_VCC.1, DISP.6, ICSP.2, J1.2, R8.2, R9.1, RB1.1, RB2.1, RB3.1, RRST.2, RTEMP.2, TEMP.3 (VDD), U$3.14 (VCC), U$3.24 (AVCC), U$3.34 (VCC1), U$3.44 (AVCC1), ZERO.1
VD_DIRECT: U$3.28 (PB4(ADC11)), VD5.1, VD6.2
ZERO_EN: U$3.25 (PD4(ICP1/ADC8))

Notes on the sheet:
3.3v on pin 4 OR 5v on pin 5
Short between Power-GND and Signal-GND
Beim P-Channel Mosfet unbedingt nochmal die Eingänge checken

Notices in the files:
parts and their libraries:
SparkFun-Passives: Licensing: Creative Commons ShareAlike 4.0 International - https://creativecommons.org/licenses/by-sa/4.0
